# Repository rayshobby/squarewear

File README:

SquareWear is an open-source wearable electronics controller board. This repository contains the hardware design files, software library, and software demo.

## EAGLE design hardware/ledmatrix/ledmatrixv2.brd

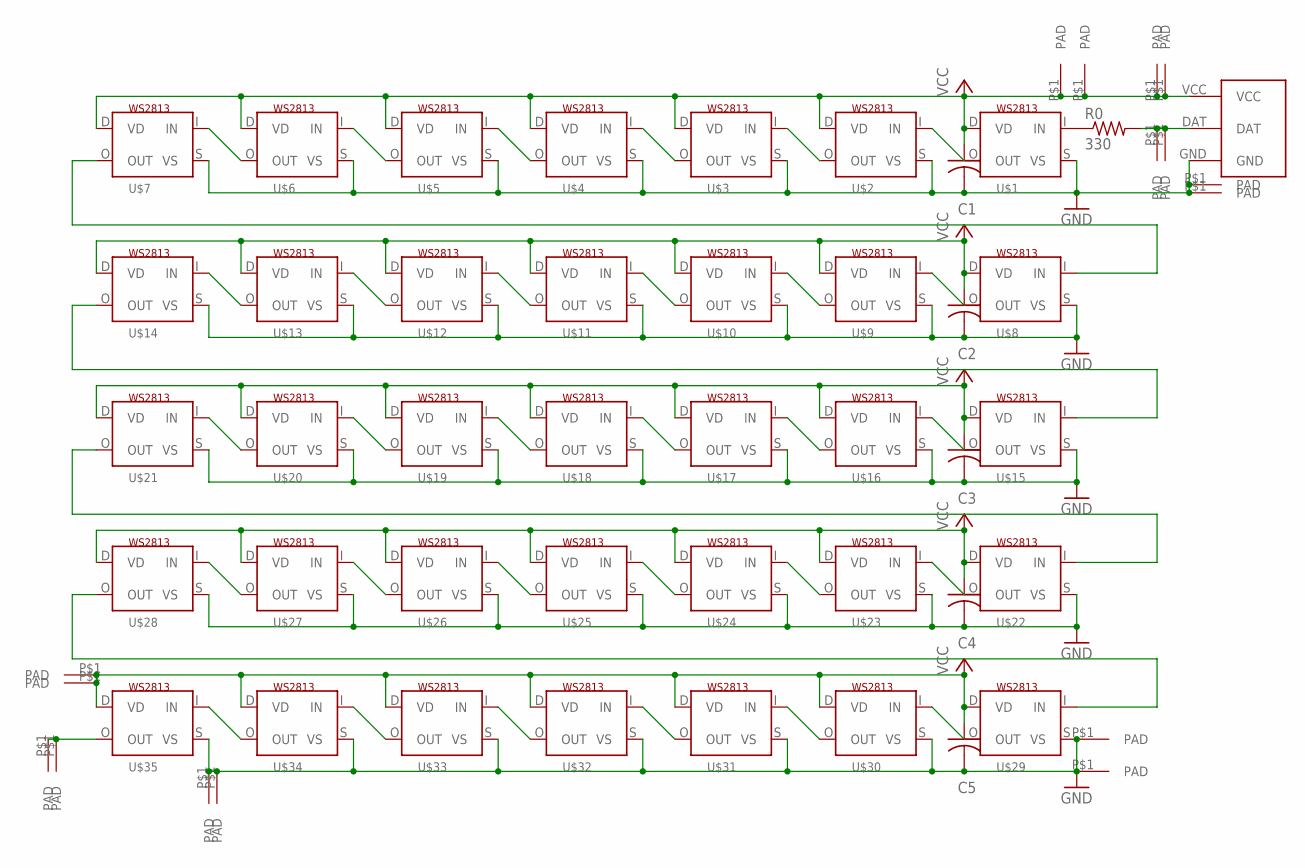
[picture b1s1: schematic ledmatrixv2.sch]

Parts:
C1, C2, C3, C4, C5: C-USC0603K; C0603K
R0: 330; R0603
U$1, U$2, U$3, U$4, U$5, U$6, U$7, U$8, U$9, U$10, U$11, U$12, U$13, U$14, U$15, U$16, U$17, U$18, U$19, U$20, U$21, U$22, U$23, U$24, U$25, U$26, U$27, U$28, U$29, U$30, U$31, U$32, U$33, U$34, U$35: WS2813; RGBLED5050_4
U$36: SQWMINI-MATRIX
U$37, U$38, U$39, U$40, U$41, U$42, U$43, U$44, U$45, U$46, U$47, U$48, U$49, U$50, U$51, U$52: TESTPAD

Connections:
DATIN: R0.2, U$36.DAT, U$41.P$1, U$42.P$1
DATOUT: U$35.O (OUT), U$47.P$1, U$48.P$1
GND: C1.2, C2.2, C3.2, C4.2, C5.2, U$1.S (VS), U$2.S (VS), U$3.S (VS), U$4.S (VS), U$5.S (VS), U$6.S (VS), U$7.S (VS), U$8.S (VS), U$9.S (VS), U$10.S (VS), U$11.S (VS), U$12.S (VS), U$13.S (VS), U$14.S (VS), U$15.S (VS), U$16.S (VS), U$17.S (VS), U$18.S (VS), U$19.S (VS), U$20.S (VS), U$21.S (VS), U$22.S (VS), U$23.S (VS), U$24.S (VS), U$25.S (VS), U$26.S (VS), U$27.S (VS), U$28.S (VS), U$29.S (VS), U$30.S (VS), U$31.S (VS), U$32.S (VS), U$33.S (VS), U$34.S (VS), U$35.S (VS), U$36.GND, U$39.P$1, U$40.P$1, U$45.P$1, U$46.P$1, U$50.P$1, U$52.P$1
unnamed: U$2.O (OUT), U$3.I (IN)
unnamed: U$1.O (OUT), U$2.I (IN)
unnamed: U$4.O (OUT), U$5.I (IN)
unnamed: U$22.O (OUT), U$23.I (IN)
unnamed: U$6.O (OUT), U$7.I (IN)
unnamed: U$3.O (OUT), U$4.I (IN)
unnamed: U$8.O (OUT), U$9.I (IN)
unnamed: U$7.O (OUT), U$8.I (IN)
unnamed: U$5.O (OUT), U$6.I (IN)
unnamed: U$9.O (OUT), U$10.I (IN)
unnamed: U$10.O (OUT), U$11.I (IN)
unnamed: U$11.O (OUT), U$12.I (IN)
unnamed: U$13.O (OUT), U$14.I (IN)
unnamed: U$12.O (OUT), U$13.I (IN)
unnamed: U$15.O (OUT), U$16.I (IN)
unnamed: U$14.O (OUT), U$15.I (IN)
unnamed: U$16.O (OUT), U$17.I (IN)
unnamed: U$17.O (OUT), U$18.I (IN)
unnamed: U$18.O (OUT), U$19.I (IN)
unnamed: U$20.O (OUT), U$21.I (IN)
unnamed: U$19.O (OUT), U$20.I (IN)
unnamed: U$23.O (OUT), U$24.I (IN)
unnamed: R0.1, U$1.I (IN)
unnamed: U$24.O (OUT), U$25.I (IN)
unnamed: U$25.O (OUT), U$26.I (IN)
unnamed: U$27.O (OUT), U$28.I (IN)
unnamed: U$26.O (OUT), U$27.I (IN)
unnamed: U$21.O (OUT), U$22.I (IN)
unnamed: U$29.O (OUT), U$30.I (IN)
unnamed: U$30.O (OUT), U$31.I (IN)
unnamed: U$31.O (OUT), U$32.I (IN)
unnamed: U$32.O (OUT), U$33.I (IN)
unnamed: U$34.O (OUT), U$35.I (IN)
unnamed: U$33.O (OUT), U$34.I (IN)
unnamed: U$28.O (OUT), U$29.I (IN)
VCC: C1.1, C2.1, C3.1, C4.1, C5.1, U$1.D (VD), U$2.D (VD), U$3.D (VD), U$4.D (VD), U$5.D (VD), U$6.D (VD), U$7.D (VD), U$8.D (VD), U$9.D (VD), U$10.D (VD), U$11.D (VD), U$12.D (VD), U$13.D (VD), U$14.D (VD), U$15.D (VD), U$16.D (VD), U$17.D (VD), U$18.D (VD), U$19.D (VD), U$20.D (VD), U$21.D (VD), U$22.D (VD), U$23.D (VD), U$24.D (VD), U$25.D (VD), U$26.D (VD), U$27.D (VD), U$28.D (VD), U$29.D (VD), U$30.D (VD), U$31.D (VD), U$32.D (VD), U$33.D (VD), U$34.D (VD), U$35.D (VD), U$36.VCC, U$37.P$1, U$38.P$1, U$43.P$1, U$44.P$1, U$49.P$1, U$51.P$1

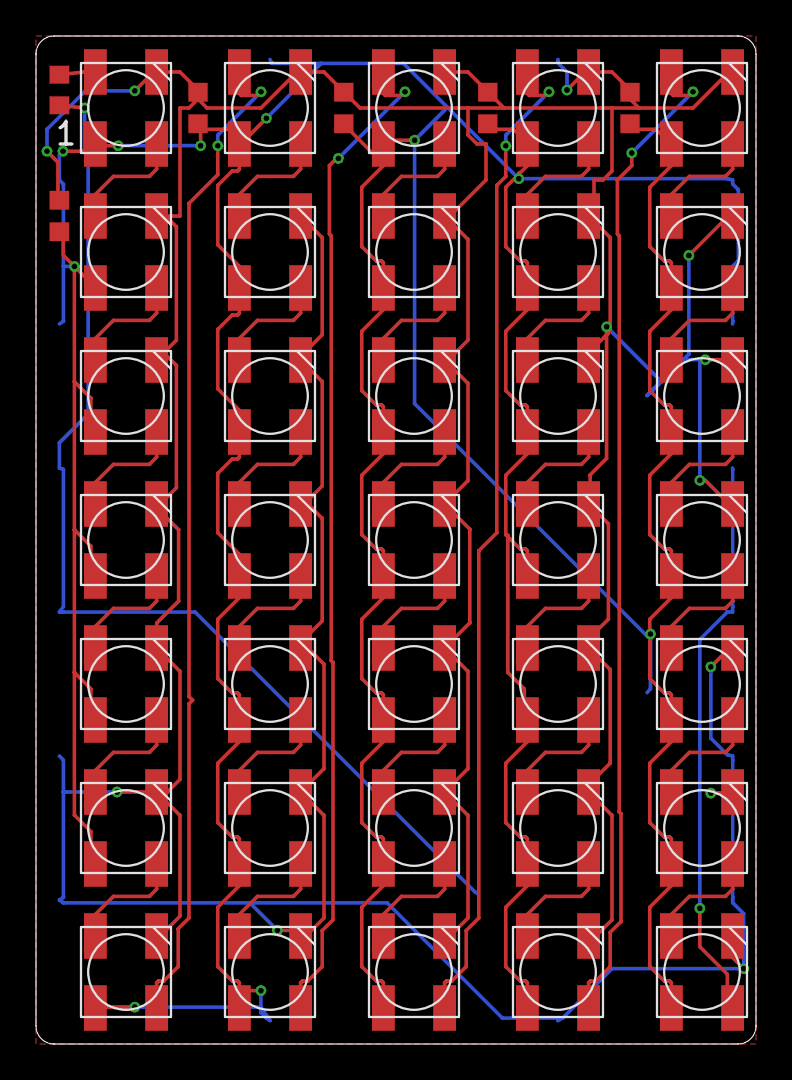
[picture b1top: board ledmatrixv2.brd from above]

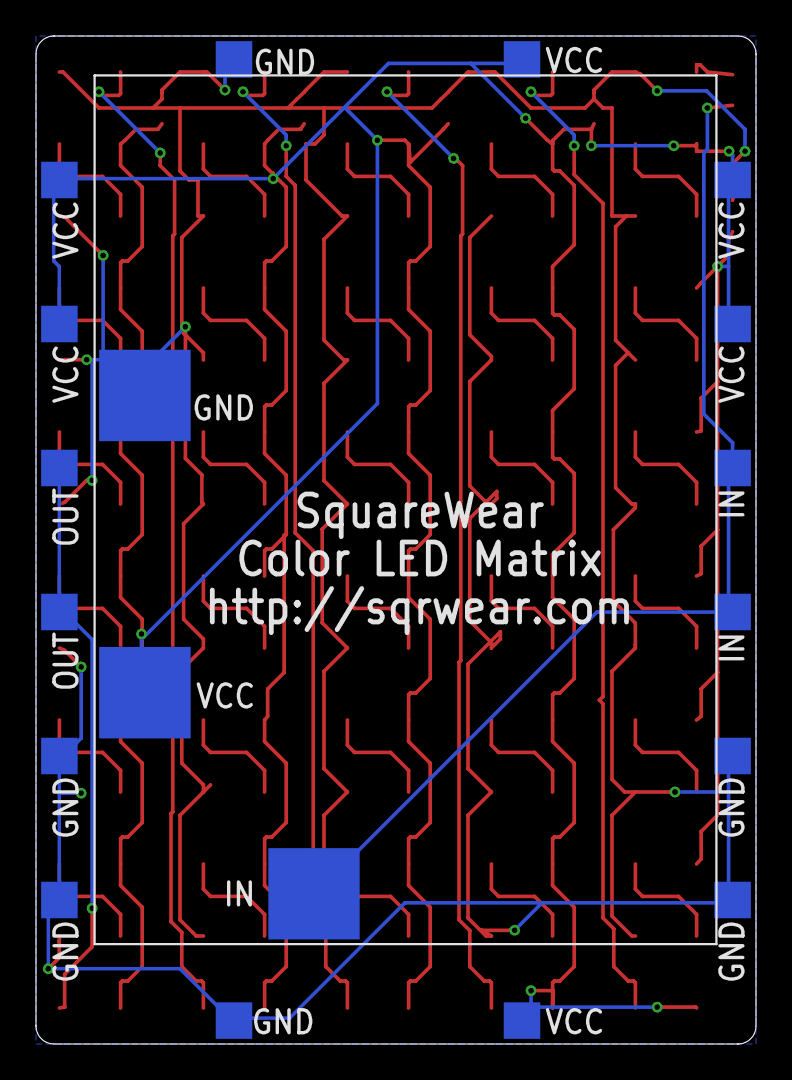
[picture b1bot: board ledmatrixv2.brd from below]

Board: 2 copper layers, 40.0 x 56.0 mm, 58 parts (17 on the bottom side), 39 nets.

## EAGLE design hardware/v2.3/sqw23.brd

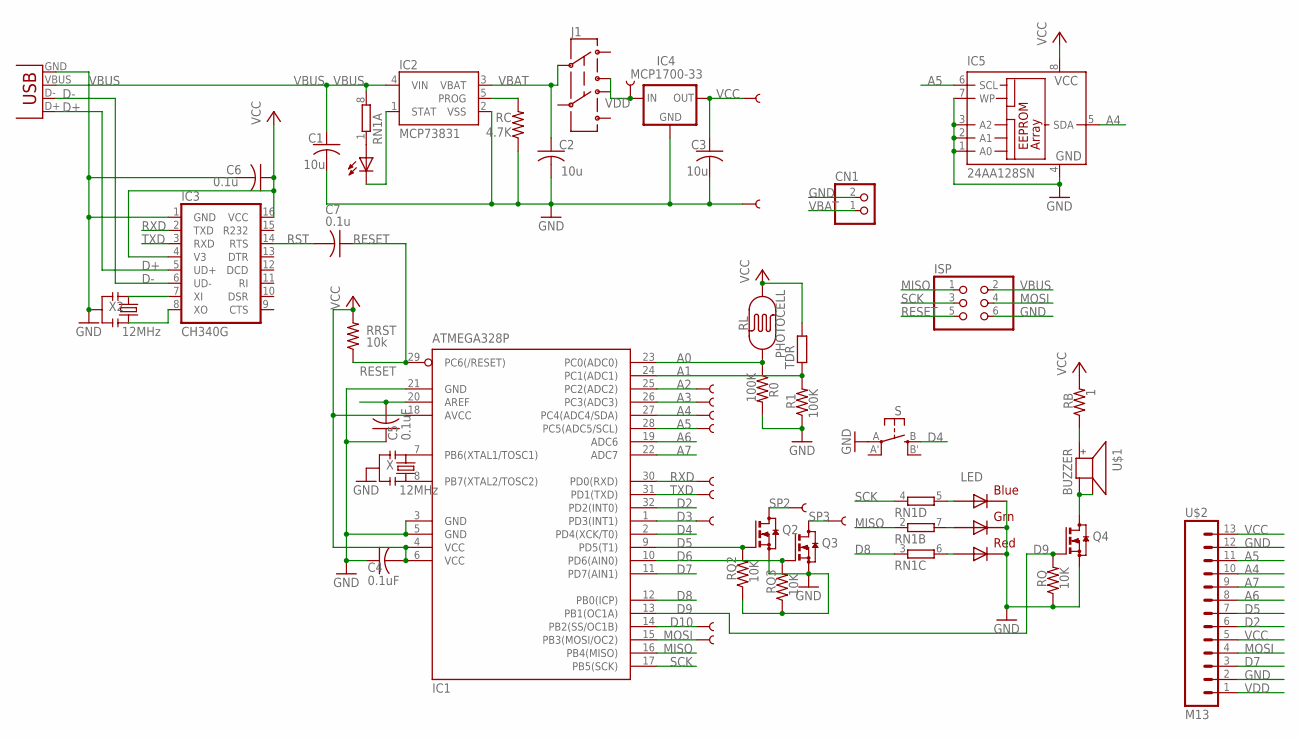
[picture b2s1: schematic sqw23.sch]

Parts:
C1, C2, C3: 10u; C0805K
C4, C5: 0.1uF; C0805K
C6, C7: 0.1u; C0805K
CHG: 0805; CHIPLED_0805
CN1: JST_2PIN-SMT-RA; JST-PH-2-SMT-RA
IC1: ATMEGA328P; TQFP32-08
IC2: MCP73831; SOT23-5
IC3: CH340G; SO16
IC4: MCP1700-33; SOT89
IC5: 24AA128SN; SO-08
ISP: PINHD-2X3; 2X03
J1: AYZ0202
LED: RGBLED5050
PAD_3, PAD_10: SEWTAP6; PETAL-SMALL-2SIDE11
PAD_5, PAD_6, PAD_11: SEWTAP6; PETAL-SMALL-2SIDE1
PAD_A2, PAD_A3: SEWTAP6; PETAL-SMALL-2SIDE1
PAD_A4, PAD_A5: SEWTAP6; PETAL-SMALL-2SIDE11
PAD_GND: SEWTAP6; PETAL-SMALL-2SIDE11
PAD_RXD: SEWTAP61; PETAL-SMALL-2SIDE1
PAD_TXD: SEWTAP6; PETAL-SMALL-2SIDE1
PAD_VBAT: SEWTAP6; PETAL-SMALL-2SIDE1
PAD_VCC: SEWTAP6; PETAL-SMALL-2SIDE11
Q2, Q3, Q4: BSS123; SOT23
R0, R1: 100K; R0805
RB: 1; R0805
RC: 4.7K; R0805
RL: PHOTOCELL
RN1: 4R-NEXB38V; EXB38V
RQ, RQ2, RQ3: 10K; R0805
RRST: 10k; R0805
S: EVQQ2; EVQ-Q2
TDR: R-EU_V526-0; V526-0
U$1: BUZZER; SMT-8585-BUZZER
U$2: M13; 1X13
X, X2: 12MHz; RESONATOR-SMD
X1: USBSMD; USB-MINIB

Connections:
A0: IC1.23 (PC0(ADC0)), R0.1, RL.1
A1: IC1.24 (PC1(ADC1)), R1.2, TDR.1
A2: IC1.25 (PC2(ADC2)), PAD_A2.1
A3: IC1.26 (PC3(ADC3)), PAD_A3.1
A4: IC1.27 (PC4(ADC4/SDA)), IC5.5 (SDA), PAD_A4.1, U$2.10
A5: IC1.28 (PC5(ADC5/SCL)), IC5.6 (SCL), PAD_A5.1, U$2.11
A6: IC1.19 (ADC6), U$2.8
A7: IC1.22 (ADC7), U$2.9
AREF: C5.2, IC1.20 (AREF)
D2: IC1.32 (PD2(INT0)), U$2.6
D3: IC1.1 (PD3(INT1)), PAD_3.1
D4: IC1.2 (PD4(XCK/T0)), S.B (S)
D5: IC1.9 (PD5(T1)), Q2.1 (G), RQ2.2, U$2.7
D6: IC1.10 (PD6(AIN0)), Q3.1 (G), RQ3.2
D7: IC1.11 (PD7(AIN1)), U$2.3
D8: IC1.12 (PB0(ICP)), RN1.3 (1)
D9: IC1.13 (PB1(OC1A)), Q4.1 (G), RQ.2
D10: IC1.14 (PB2(SS/OC1B)), PAD_10.1
D+: IC3.5 (UD+), X1.D+
D-: IC3.6 (UD-), X1.D-
GND: C1.2, C2.2, C3.2, C4.1, C5.1, C6.2, CN1.2 (1), IC1.3 (GND), IC1.5 (GND), IC1.21 (GND), IC2.2 (VSS), IC3.1 (GND), IC4.1 (GND), IC5.1 (A0), IC5.2 (A1), IC5.3 (A2), IC5.4 (GND), IC5.7 (WP), ISP.6, LED.4 (BLUE_C), LED.5 (RED_C), LED.6 (GREEN_C), PAD_GND.1, Q2.2 (S), Q3.2 (S), Q4.2 (S), R0.2, R1.1, RC.1, RQ.1, RQ2.1, RQ3.1, S.A, U$2.2, U$2.12, X.2, X1.GND, X2.2
MISO: IC1.16 (PB4(MISO)), ISP.1, RN1.2 (1)
MOSI: IC1.15 (PB3(MOSI/OC2)), ISP.4, PAD_11.1, U$2.4
unnamed: IC1.8 (PB7(XTAL2/TOSC2)), X.3
unnamed: IC1.7 (PB6(XTAL1/TOSC1)), X.1
unnamed: LED.3 (BLUE_A), RN1.5 (2)
unnamed: CHG.A, RN1.1
unnamed: CHG.C, IC2.1 (STAT)
unnamed: IC2.5 (PROG), RC.2
unnamed: Q4.3 (D), U$1.-, U$1.A-
unnamed: LED.1 (GREEN_A), RN1.7 (2)
unnamed: LED.2 (RED_A), RN1.6 (2)
unnamed: IC3.7 (XI), X2.1
unnamed: RB.1, U$1.+
unnamed: IC3.8 (XO), X2.3
RESET: C7.1, IC1.29 (PC6(/RESET)), ISP.5, RRST.1
RST: C7.2, IC3.14 (RTS)
RXD: IC1.30 (PD0(RXD)), IC3.2 (TXD), PAD_RXD.1
SCK: IC1.17 (PB5(SCK)), ISP.3, RN1.4 (1)
SP2: PAD_5.1, Q2.3 (D)
SP3: PAD_6.1, Q3.3 (D)
TXD: IC1.31 (PD1(TXD)), IC3.3 (RXD), PAD_TXD.1
VBAT: C2.1, CN1.1 (2), IC2.3 (VBAT), J1.2
VBUS: C1.1, IC2.4 (VIN), ISP.2, RN1.8 (2), X1.VBUS
VCC: C3.1, C4.2, C6.1, IC1.4 (VCC), IC1.6 (VCC), IC1.18 (AVCC), IC3.4 (V3), IC3.16 (VCC), IC4.3 (OUT), IC5.8 (VCC), PAD_VCC.1, RB.2, RL.2, RRST.2, TDR.2, U$2.5, U$2.13
VDD: IC4.2 (IN), J1.1 (3), PAD_VBAT.1, U$2.1

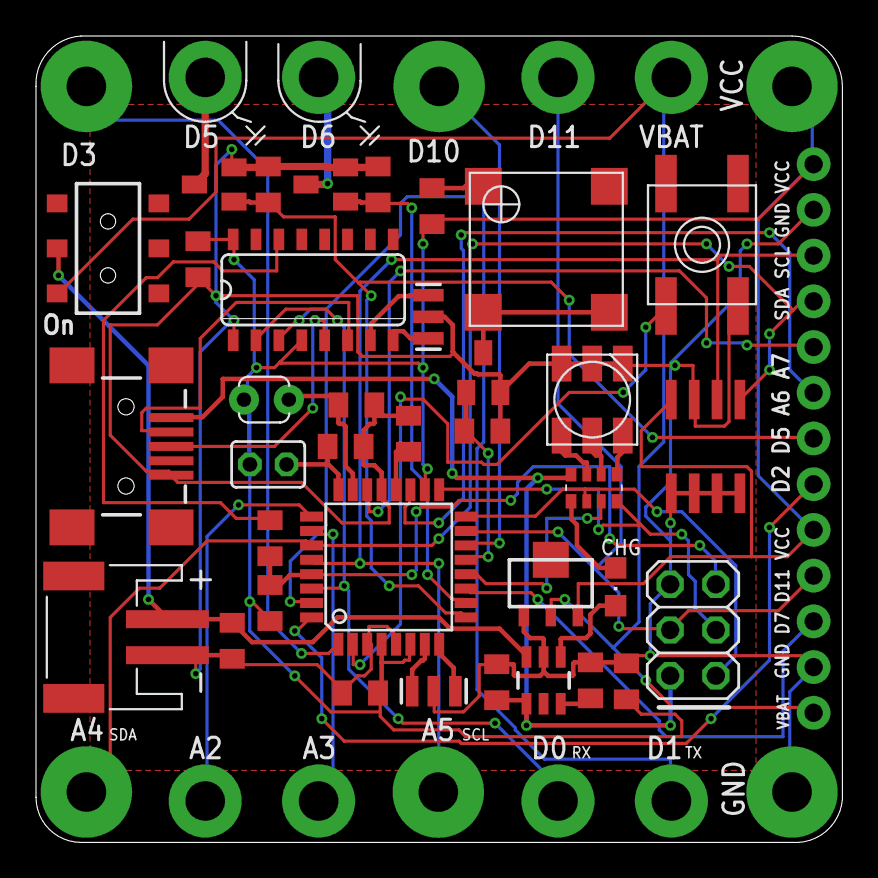
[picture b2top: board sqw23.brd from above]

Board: 2 copper layers, 44.8 x 44.8 mm, 51 parts (0 on the bottom side), 46 nets.

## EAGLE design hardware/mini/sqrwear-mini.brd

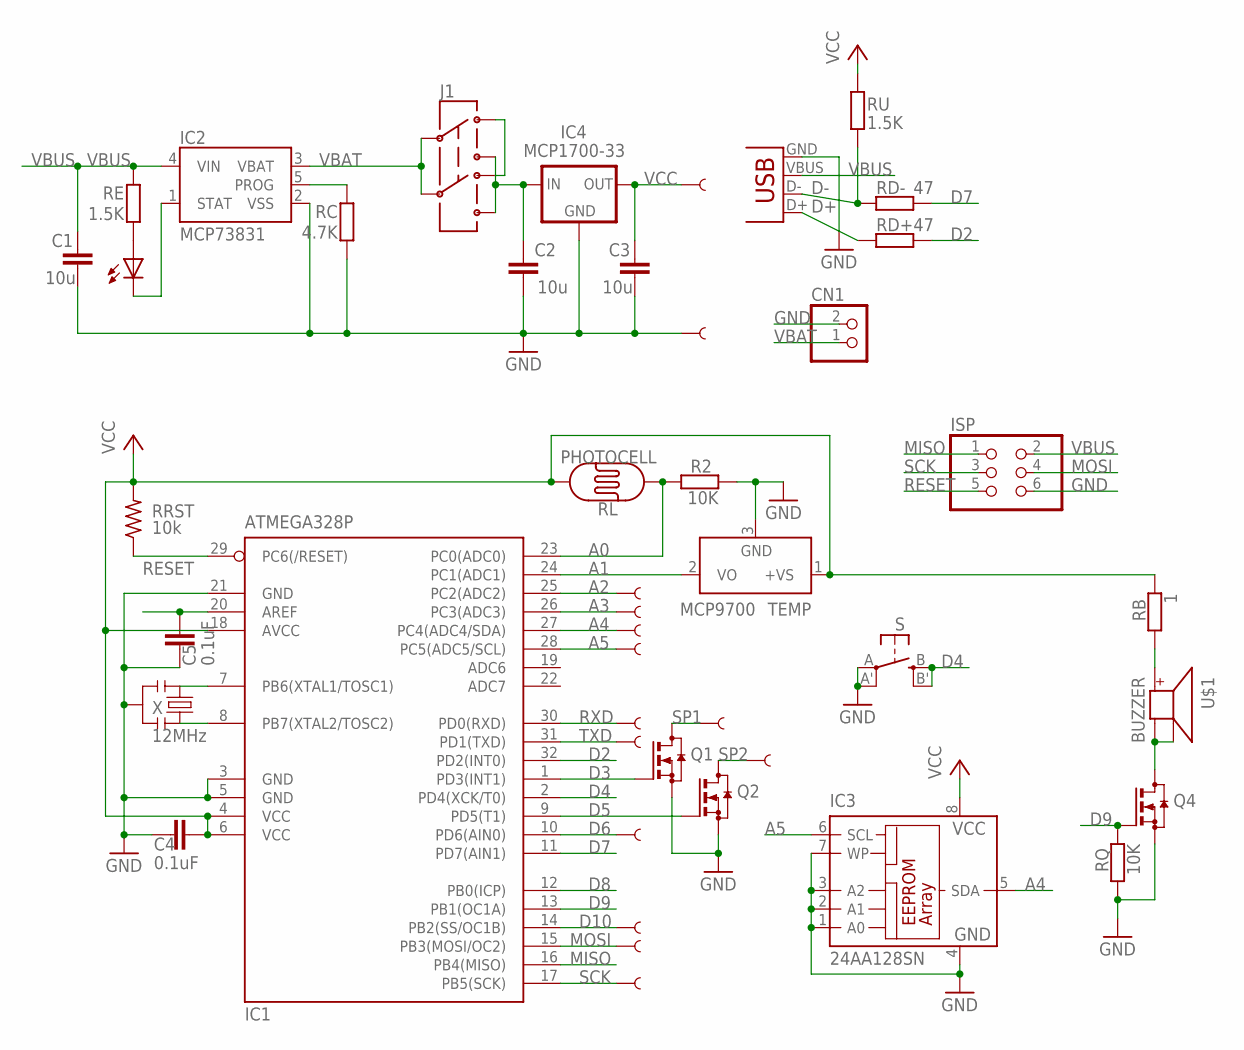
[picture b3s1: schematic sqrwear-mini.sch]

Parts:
C1, C2, C3: 10u; C0805K
C4, C5: 0.1uF; C0805K
CHG: 0805; CHIPLED_0805
CN1: JST_2PIN-SMT-RA; JST-PH-2-SMT-RA
IC1: ATMEGA328P; TQFP32-08
IC2: MCP73831; SOT23-5
IC3: 24AA128SN; SO-08
IC4: MCP1700-33; SOT23
ISP: PINHD-2X3; 2X03
J1: AYZ0202
PAD_3, PAD_10: SEWTAP6; PETAL-SMALL-2SIDE11
PAD_5, PAD_6, PAD_11, PAD_13: SEWTAP6; PETAL-SMALL-2SIDE1
PAD_A2, PAD_A3: SEWTAP6; PETAL-SMALL-2SIDE1
PAD_A4, PAD_A5: SEWTAP6; PETAL-SMALL-2SIDE11
PAD_GND: SEWTAP6; PETAL-SMALL-2SIDE11
PAD_RXD: SEWTAP61; PETAL-SMALL-2SIDE1
PAD_TXD: SEWTAP6; PETAL-SMALL-2SIDE1
PAD_VCC: SEWTAP6; PETAL-SMALL-2SIDE11
Q1, Q2, Q4: BSS123; SOT23
R2: 10K; R0805
RB: 1; R0805
RC: 4.7K; R0805
RD+: 47; R0805
RD-: 47; R0805
RE: 1.5K; R0805
RL: PHOTOCELL
RQ: 10K; R0805
RRST: 10k; R0805
RU: 1.5K; R0805
S: EVQQ2; EVQ-Q2
TEMP: MCP9700; SOT23
U$1: BUZZER; SMT-8585-BUZZER
X: 12MHz; RESONATOR-SMD
X1: USBSMD; USB-MINIB

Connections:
A0: IC1.23 (PC0(ADC0)), R2.1, RL.1
A1: IC1.24 (PC1(ADC1)), TEMP.2 (VO)
A2: IC1.25 (PC2(ADC2)), PAD_A2.1
A3: IC1.26 (PC3(ADC3)), PAD_A3.1
A4: IC1.27 (PC4(ADC4/SDA)), IC3.5 (SDA), PAD_A4.1
A5: IC1.28 (PC5(ADC5/SCL)), IC3.6 (SCL), PAD_A5.1
AREF: C5.2, IC1.20 (AREF)
D2: IC1.32 (PD2(INT0)), RD+.2
D3: IC1.1 (PD3(INT1)), Q1.1 (G)
D4: IC1.2 (PD4(XCK/T0)), S.B (S), S.B' (S1)
D5: IC1.9 (PD5(T1)), Q2.1 (G)
D6: IC1.10 (PD6(AIN0)), PAD_6.1
D7: IC1.11 (PD7(AIN1)), RD-.2
D8: IC1.12 (PB0(ICP))
D9: IC1.13 (PB1(OC1A)), Q4.1 (G), RQ.2
D10: IC1.14 (PB2(SS/OC1B)), PAD_10.1
D+: RD+.1, X1.D+
D-: RD-.1, RU.1, X1.D-
GND: C1.2, C2.2, C3.2, C4.1, C5.1, CN1.2 (1), IC1.3 (GND), IC1.5 (GND), IC1.21 (GND), IC2.2 (VSS), IC3.1 (A0), IC3.2 (A1), IC3.3 (A2), IC3.4 (GND), IC3.7 (WP), IC4.1 (GND), ISP.6, PAD_GND.1, Q1.2 (S), Q2.2 (S), Q4.2 (S), R2.2, RC.1, RQ.1, S.A, S.A' (P1), TEMP.3 (GND), X.2, X1.GND
MISO: IC1.16 (PB4(MISO)), ISP.1
MOSI: IC1.15 (PB3(MOSI/OC2)), ISP.4, PAD_11.1
unnamed: J1.3 (1), J1.6 (4)
unnamed: IC1.7 (PB6(XTAL1/TOSC1)), X.1
unnamed: IC1.8 (PB7(XTAL2/TOSC2)), X.3
unnamed: CHG.A, RE.1
unnamed: CHG.C, IC2.1 (STAT)
unnamed: IC2.5 (PROG), RC.2
unnamed: Q4.3 (D), U$1.-, U$1.A-
unnamed: RB.1, U$1.+
RESET: IC1.29 (PC6(/RESET)), ISP.5, RRST.1
RXD: IC1.30 (PD0(RXD)), PAD_RXD.1
SCK: IC1.17 (PB5(SCK)), ISP.3, PAD_13.1
SP1: PAD_3.1, Q1.3 (D)
SP2: PAD_5.1, Q2.3 (D)
TXD: IC1.31 (PD1(TXD)), PAD_TXD.1
VBAT: CN1.1 (2), IC2.3 (VBAT), J1.2, J1.5
VBUS: C1.1, IC2.4 (VIN), ISP.2, RE.2, X1.VBUS
VCC: C3.1, C4.2, IC1.4 (VCC), IC1.6 (VCC), IC1.18 (AVCC), IC3.8 (VCC), IC4.2 (OUT), PAD_VCC.1, RB.2, RL.2, RRST.2, RU.2, TEMP.1 (+VS)
VDD: C2.1, IC4.3 (IN), J1.1 (3), J1.4 (6)

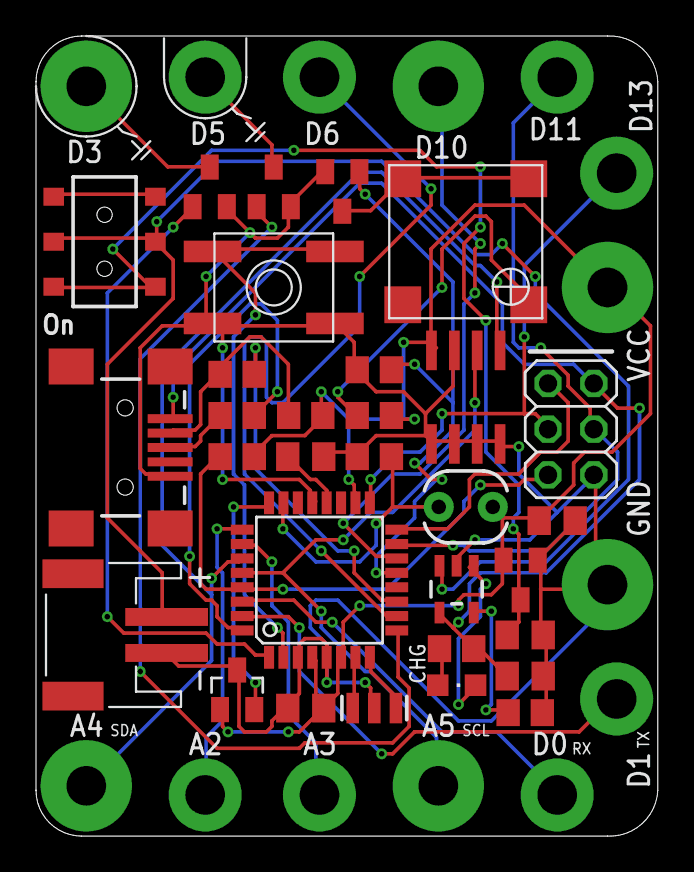
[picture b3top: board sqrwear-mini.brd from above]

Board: 2 copper layers, 34.5 x 44.5 mm, 45 parts (0 on the bottom side), 38 nets.

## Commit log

2012-10-12 initial checkin
2013-10-06 check in SquareWear 2.0 hardware design files. Move SquareWear 1.1 to sub-folder
2013-10-06 Add SquareWear 2.0 software package, bootloader, HID serial monitor, and usbasp driver for Windows
2013-10-06 Add GettingStarted.pdf to SquareWear v2.0 software folder
2013-12-02 update squarewear 2.0 user manual
2013-12-02 add readme.txt to software/v2.0 folder
2013-12-02 re-organize docs folder
2013-12-02 update library examples
2014-01-20 add digital_piano demo
2014-02-10 update user manual
2014-02-10 check in SquareWear Mini hardware design files
2014-02-10 add new SquareWear2 libraries
2014-02-10 add flipbookHost Processing software
2014-02-10 update SquareWear Mini and LED Matrix hardware design files
2014-04-26 check in SquareWear 1.1 demo code
2014-04-26 re-checkin mini hardware design files
2014-11-19 check in hardware 2.3 design files
2016-10-30 add version 2 design files
